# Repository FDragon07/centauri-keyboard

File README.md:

# Description of My Project
This project is my take on a keyboad; it is orthognal, low profile keyboard with fancy knobs (cause who doesn't like knobs).
The reason I made this project is beacuse I have never loved the keyboard I have had for years now, and I have always wanted to try an orthongnal keyboard. This keyboard is based on the creator keyboard by work louder but I am not paying $350 for a keyboard when I can just build one!

# Bill of Materials

| Designation         | Price   | Shipping | Tariffs | Supplier / Reference                                                                                      |
|---------------------|---------|----------|---------|------------------------------------------------------------------------------------------------------------|
| 482020514001 (Encoder)| $4.00  | $7.99    | $0.00   | [Mouser](https://www.mouser.com/ProductDetail/Wurth-Elektronik/482020514001?qs=2WXlatMagcGAwM91AS9d8A%3D%3D) |
| Keyswitch           | $54.25  | $11.18   | $0.00   | [LowProKB](https://lowprokb.ca/products/sunset-tactile-choc-switches?variant=41955920248996) |
| Display (~)         | $4.73   | $8.12    | $0.00   | [BuyDisplay](https://www.buydisplay.com/1-3-inch-tft-ips-lcd-display-module-240x240-spi-for-arduino-raspberry-pi) |
| 100 (misc)          | $0.00   | $0.00    | $0.00   | me |
| Diode               | $3.15   | $0.00    | $0.00   | [Mouser](https://www.mouser.com/ProductDetail/637-1N4148W)|
| Raspberry Pi Pico   | $4.00   | $6.25    | $0.00   | [PiShop](https://www.pishop.us) |
| PCB                 | $14.30  | $46.12   | $7.87   | JLCPCB |

#### Total Price:
##### $171.96

# Screenshot of My Project
### Schematic, PCB, CAD

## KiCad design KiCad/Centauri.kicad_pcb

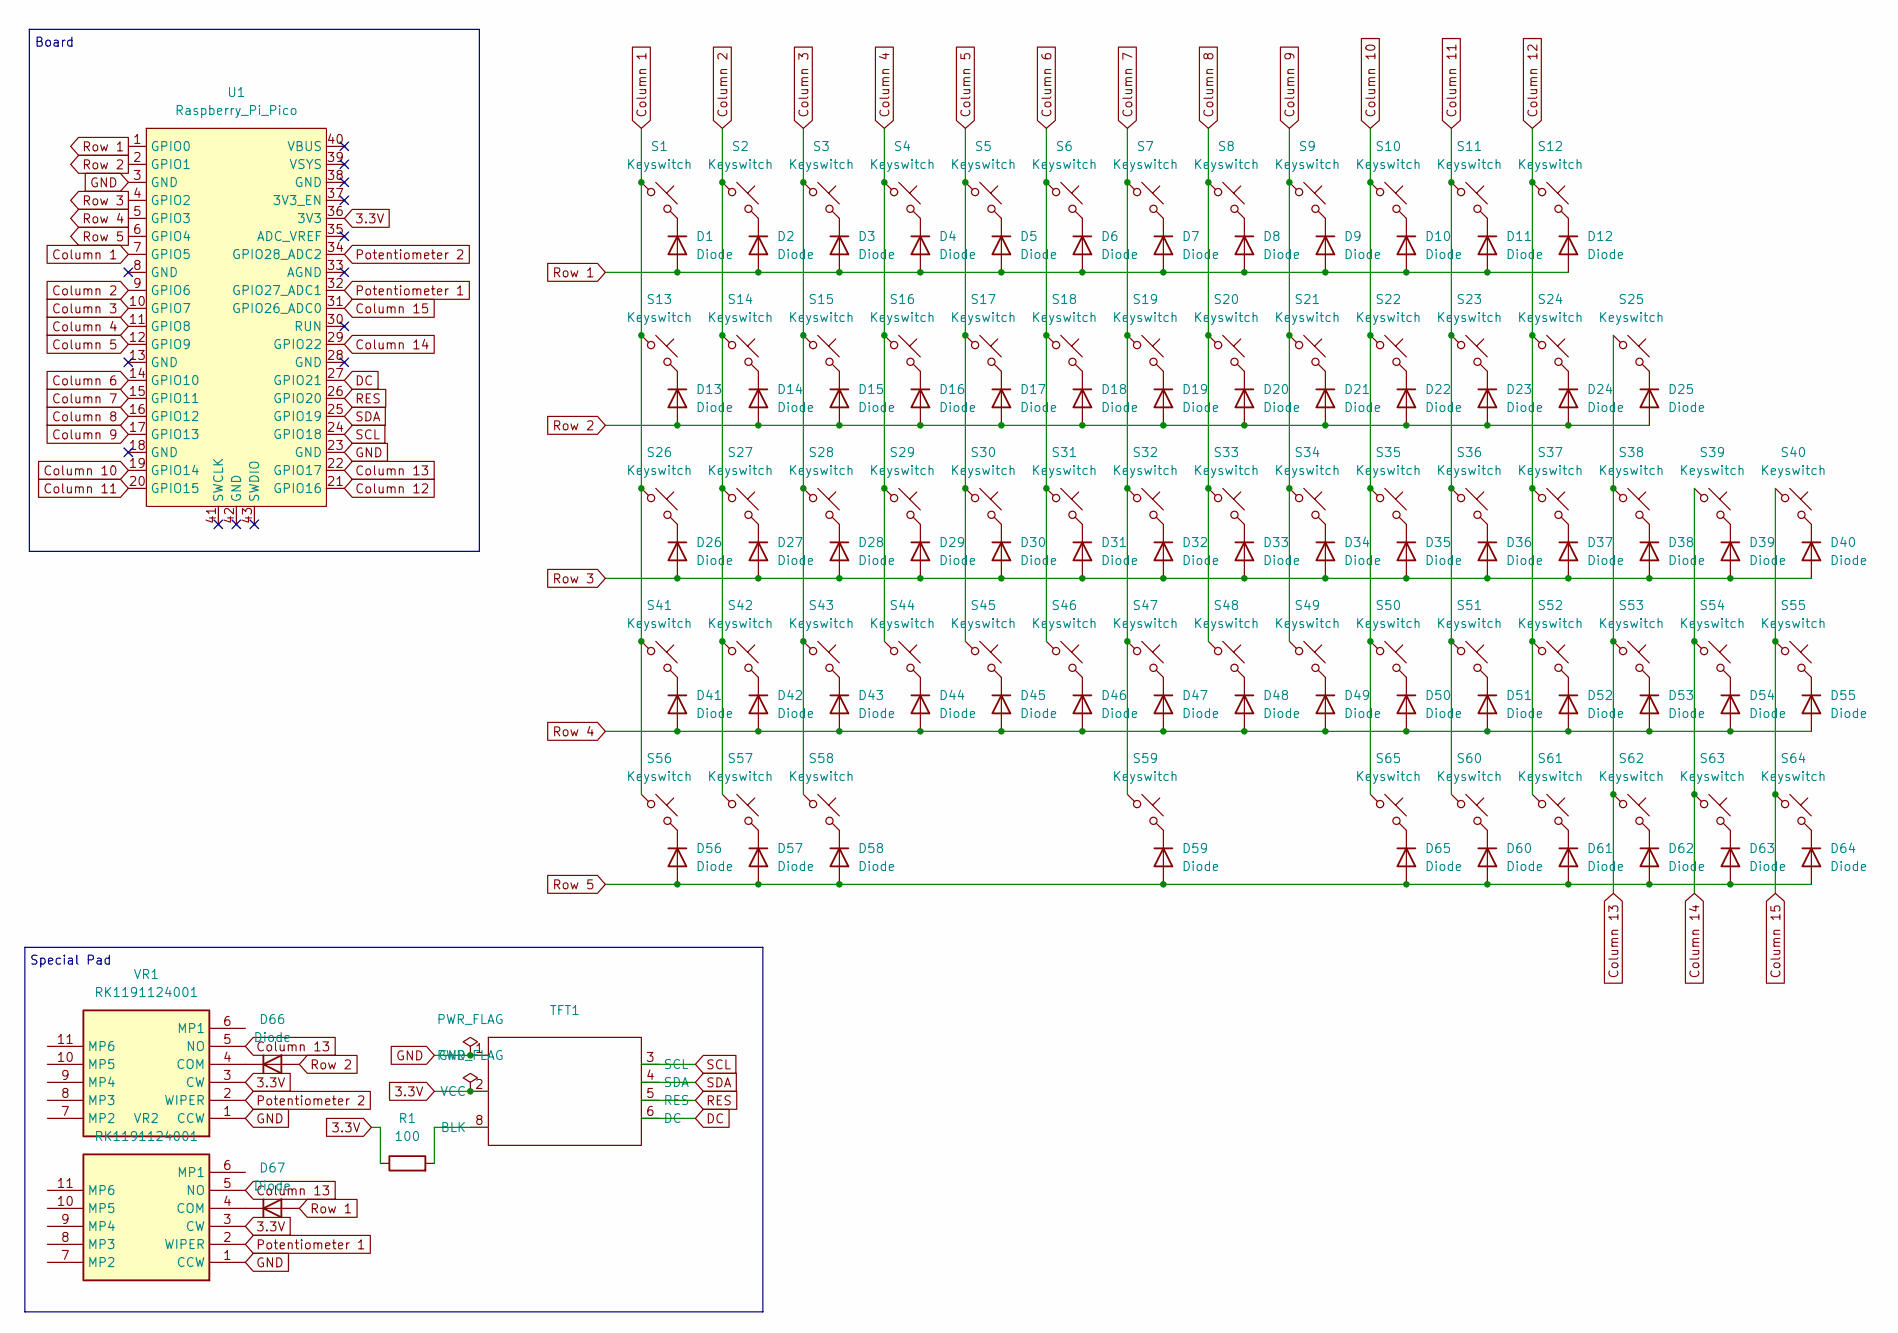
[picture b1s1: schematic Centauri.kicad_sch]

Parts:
D1, D2, D3, D4, D5, D6, D7, D8, D9, D10, D11, D12, D13, D14, D15, D16, D17, D18, D19, D20, D21, D22, D23, D24, D25, D26, D27, D28, D29, D30, D31, D32, D33, D34, D35, D36, D37, D38, D39, D40, D41, D42, D43, D44, D45, D46, D47, D48, D49, D50, D51, D52, D53, D54, D55, D56, D57, D58, D59, D60, D61, D62, D63, D64, D65, D66, D67: Diode; Diode_SOD-123
R1: 100; Resistor_0402
S1, S2, S3, S4, S5, S6, S7, S8, S9, S10, S11, S13, S14, S15, S16, S17, S18, S19, S20, S21, S22, S23, S24, S25, S26, S27, S28, S29, S30, S31, S32, S33, S34, S35, S36, S37, S38, S39, S42, S43, S44, S45, S46, S47, S48, S49, S50, S51, S52, S53, S54, S55, S60, S61, S62, S63, S64, S65: Keyswitch; Choc_V1_1.00u
S12, S40, S41: Keyswitch; Choc_V1_2.00u
S56, S57, S58: Keyswitch; Choc_V1_1.25u
S59: Keyswitch; Choc_V1_6.25u
TFT1: TFT_1.3_SPI_Module
U1: Raspberry_Pi_Pico; RaspberryPi_Pico_SMD_HandSolder
VR1, VR2: RK1191124001; Mouser Part Number 688-RK1191124001

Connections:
3.3V: R1.1, TFT1.2 (VCC), U1.36 (3V3), VR1.3 (CW), VR2.3 (CW)
Column 1: S1.1, S13.1, S26.1, S41.1, S56.1, U1.7 (GPIO5)
Column 2: S2.1, S14.1, S27.1, S42.1, S57.1, U1.9 (GPIO6)
Column 3: S3.1, S15.1, S28.1, S43.1, S58.1, U1.10 (GPIO7)
Column 4: S4.1, S16.1, S29.1, S44.1, U1.11 (GPIO8)
Column 5: S5.1, S17.1, S30.1, S45.1, U1.12 (GPIO9)
Column 6: S6.1, S18.1, S31.1, S46.1, U1.14 (GPIO10)
Column 7: S7.1, S19.1, S32.1, S47.1, S59.1, U1.15 (GPIO11)
Column 8: S8.1, S20.1, S33.1, S48.1, U1.16 (GPIO12)
Column 9: S9.1, S21.1, S34.1, S49.1, U1.17 (GPIO13)
Column 10: S10.1, S22.1, S35.1, S50.1, S65.1, U1.19 (GPIO14)
Column 11: S11.1, S23.1, S36.1, S51.1, S60.1, U1.20 (GPIO15)
Column 12: S12.1, S24.1, S37.1, S52.1, S61.1, U1.21 (GPIO16)
Column 13: S25.1, S38.1, S53.1, S62.1, U1.22 (GPIO17), VR1.5 (NO), VR2.5 (NO)
Column 14: S39.1, S54.1, S63.1, U1.29 (GPIO22)
Column 15: S40.1, S55.1, S64.1, U1.31 (GPIO26_ADC0)
DC: TFT1.6 (DC), U1.27 (GPIO21)
GND: TFT1.1 (GND), U1.3 (GND), U1.23 (GND), VR1.1 (CCW), VR2.1 (CCW)
unnamed: D1.1 (K), S1.2
unnamed: D2.1 (K), S2.2
unnamed: D3.1 (K), S3.2
unnamed: D4.1 (K), S4.2
unnamed: D5.1 (K), S5.2
unnamed: D6.1 (K), S6.2
unnamed: D7.1 (K), S7.2
unnamed: D8.1 (K), S8.2
unnamed: D9.1 (K), S9.2
unnamed: D10.1 (K), S10.2
unnamed: D11.1 (K), S11.2
unnamed: D12.1 (K), S12.2
unnamed: D13.1 (K), S13.2
unnamed: D14.1 (K), S14.2
unnamed: D15.1 (K), S15.2
unnamed: D16.1 (K), S16.2
unnamed: D17.1 (K), S17.2
unnamed: D18.1 (K), S18.2
unnamed: D19.1 (K), S19.2
unnamed: D20.1 (K), S20.2
unnamed: D21.1 (K), S21.2
unnamed: D22.1 (K), S22.2
unnamed: D23.1 (K), S23.2
unnamed: D24.1 (K), S24.2
unnamed: D25.1 (K), S25.2
unnamed: D26.1 (K), S26.2
unnamed: D27.1 (K), S27.2
unnamed: D28.1 (K), S28.2
unnamed: D29.1 (K), S29.2
unnamed: D30.1 (K), S30.2
unnamed: D31.1 (K), S31.2
unnamed: D32.1 (K), S32.2
unnamed: D33.1 (K), S33.2
unnamed: D34.1 (K), S34.2
unnamed: D35.1 (K), S35.2
unnamed: D36.1 (K), S36.2
unnamed: D37.1 (K), S37.2
unnamed: D38.1 (K), S38.2
unnamed: D39.1 (K), S39.2
unnamed: D40.1 (K), S40.2
unnamed: D41.1 (K), S41.2
unnamed: D42.1 (K), S42.2
unnamed: D43.1 (K), S43.2
unnamed: D44.1 (K), S44.2
unnamed: D45.1 (K), S45.2
unnamed: D46.1 (K), S46.2
unnamed: D47.1 (K), S47.2
unnamed: D48.1 (K), S48.2
unnamed: D49.1 (K), S49.2
unnamed: D50.1 (K), S50.2
unnamed: D51.1 (K), S51.2
unnamed: D52.1 (K), S52.2
unnamed: D53.1 (K), S53.2
unnamed: D54.1 (K), S54.2
unnamed: D55.1 (K), S55.2
unnamed: D56.1 (K), S56.2
unnamed: D57.1 (K), S57.2
unnamed: D58.1 (K), S58.2
unnamed: D59.1 (K), S59.2
unnamed: D60.1 (K), S60.2
unnamed: D61.1 (K), S61.2
unnamed: D62.1 (K), S62.2
unnamed: D63.1 (K), S63.2
unnamed: D64.1 (K), S64.2
unnamed: D65.1 (K), S65.2
unnamed: D66.1 (K), VR1.4 (COM)
unnamed: D67.1 (K), VR2.4 (COM)
unnamed: R1.2, TFT1.8 (BLK)
Potentiometer 1: U1.32 (GPIO27_ADC1), VR2.2 (WIPER)
Potentiometer 2: U1.34 (GPIO28_ADC2), VR1.2 (WIPER)
RES: TFT1.5 (RES), U1.26 (GPIO20)
Row 1: D1.2 (A), D2.2 (A), D3.2 (A), D4.2 (A), D5.2 (A), D6.2 (A), D7.2 (A), D8.2 (A), D9.2 (A), D10.2 (A), D11.2 (A), D12.2 (A), D67.2 (A), U1.1 (GPIO0)
Row 2: D13.2 (A), D14.2 (A), D15.2 (A), D16.2 (A), D17.2 (A), D18.2 (A), D19.2 (A), D20.2 (A), D21.2 (A), D22.2 (A), D23.2 (A), D24.2 (A), D25.2 (A), D66.2 (A), U1.2 (GPIO1)
Row 3: D26.2 (A), D27.2 (A), D28.2 (A), D29.2 (A), D30.2 (A), D31.2 (A), D32.2 (A), D33.2 (A), D34.2 (A), D35.2 (A), D36.2 (A), D37.2 (A), D38.2 (A), D39.2 (A), D40.2 (A), U1.4 (GPIO2)
Row 4: D41.2 (A), D42.2 (A), D43.2 (A), D44.2 (A), D45.2 (A), D46.2 (A), D47.2 (A), D48.2 (A), D49.2 (A), D50.2 (A), D51.2 (A), D52.2 (A), D53.2 (A), D54.2 (A), D55.2 (A), U1.5 (GPIO3)
Row 5: D56.2 (A), D57.2 (A), D58.2 (A), D59.2 (A), D60.2 (A), D61.2 (A), D62.2 (A), D63.2 (A), D64.2 (A), D65.2 (A), U1.6 (GPIO4)
SCL: TFT1.3 (SCL), U1.24 (GPIO18)
SDA: TFT1.4 (SDA), U1.25 (GPIO19)

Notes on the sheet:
Special Pad
Board

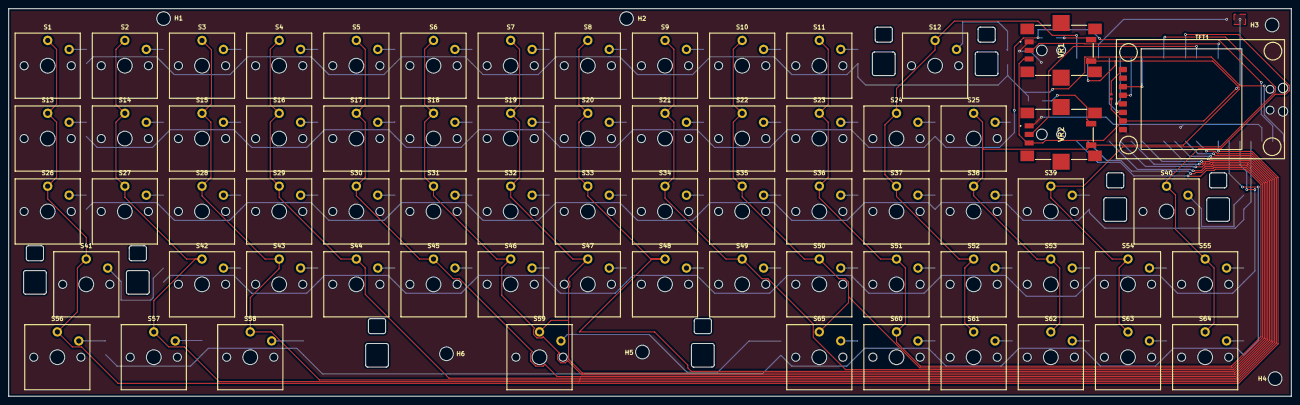
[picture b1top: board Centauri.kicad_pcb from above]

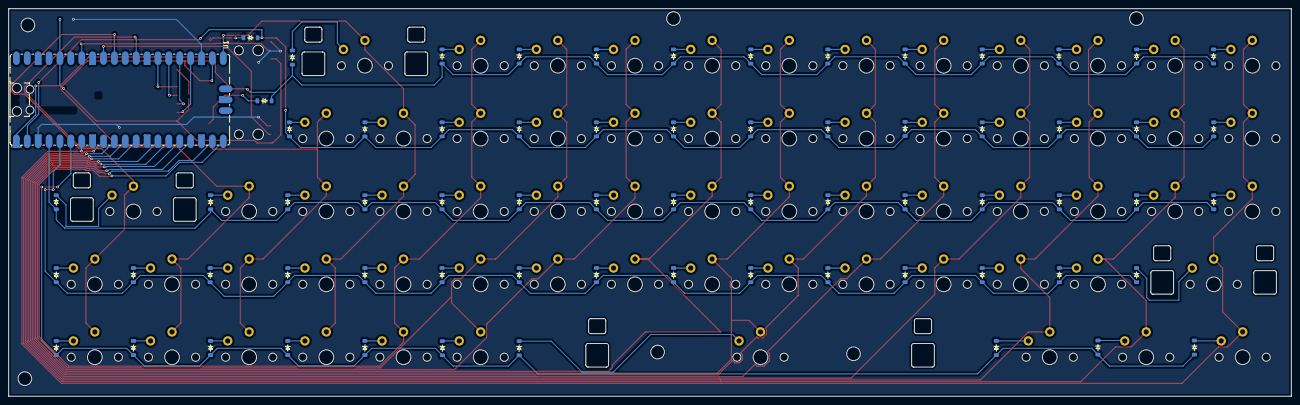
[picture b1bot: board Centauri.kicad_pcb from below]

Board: 2 copper layers, 299.2 x 90.4 mm, 143 parts (68 on the bottom side), 96 nets.

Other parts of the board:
H1, H2, H4, H5, H6: MountingHole; MountingHole_3.2mm_M3
H3: MountingHole_3.2mm_M3

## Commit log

2025-05-23 Fixed Table in README.md
2025-05-24 Updated JOURNAL
2025-05-24 spelling
2025-05-26 May 25 Journal entry
2025-05-27 Another day, another journal entry
2025-05-27 Added explations
2025-05-28 May 27th
2025-06-13 New Entry!
2025-07-06 Added case
2025-07-06 Case Files
2025-07-07 Finished!
2025-08-07 Step file of board
2025-08-07 Firmware for keyboard
2025-08-07 Update Pricing
2025-08-16 Updated Final Product
2025-08-16 Update Image
2025-08-16 Updated 3d print files
    Also added a port for the plug, forgot about that the first time around.
2025-08-16 Added Encoder
2025-08-16 Update with encoder images
